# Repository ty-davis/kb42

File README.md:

# kb42
Split 42 key keyboard utilizing Redragon low profile keys

It is heavily inspired by the [Budgy](https://github.com/doesntfazer/Budgy)
while also being influenced in design by the
[Cheapino](https://github.com/tompi/cheapino).

Build guides coming soon. Source code for the firmware
for the keyboard can be found in my [qmk fork](https://github.com/TyGuy60401/qmk_firmware).
In the assets folder you can find some pics and the
.uf2 firmware files that you can download to flash the
board yourself without having to build the entire qmk
compilation suite. One of the firmware files is a via
compatible version of the firmware for the keyboard,
and the other uses a very basic layout which is quite
limited.

Via firmware guide
------------------

Because my firmware isn't in the official via firmware
repo, in order to use via with this keyboard you will
need to follow a few extra steps the first time you
use it.

After flashing the [via specific firmware](https://github.com/TyGuy60401/kb42/blob/3ecddecb2256828aa2ff203ea3fbf5516b5cc939/assets/firmware/kb42_via.uf2)
to the keyboard and connecting the keyboard to your computer,
navigate to the [via website](usevia.app) and press `authorize
device`.  Select kb42 in the dropdown that appears and
you'll enter the app.

Usually you can start changing the keymaps to the board
at this point but we need to complete an extra step. Go to the settings
icon in the top center and enable the option
that says `Show Design Tab`. Now a new paintbrush icon
has appeared above. Select that tab and click `Load
Draft Definition`. That will prompt you to upload a
json file that corresponds to some via specific definitions
for this keyboard. Upload [this json file](https://github.com/TyGuy60401/kb42/blob/dc6ad67e50948e26156101fd82f4def80222cbb4/assets/firmware/kb42_via-definition.json)
which can be found in this repo -> assets -> firmware
-> kb42_via-definition.json

Once that file is uploaded and the via app accepts it
you'll be able to change all of the configuration for
the board. You can see the configuration that I'm using
for the board by uploading the configuration file called
[`kb42_TyGuy60401_layout.json`](https://github.com/TyGuy60401/kb42/blob/dc6ad67e50948e26156101fd82f4def80222cbb4/assets/firmware/kb42_TyGuy60401_layout.json) which can be found in
the firmware folder.

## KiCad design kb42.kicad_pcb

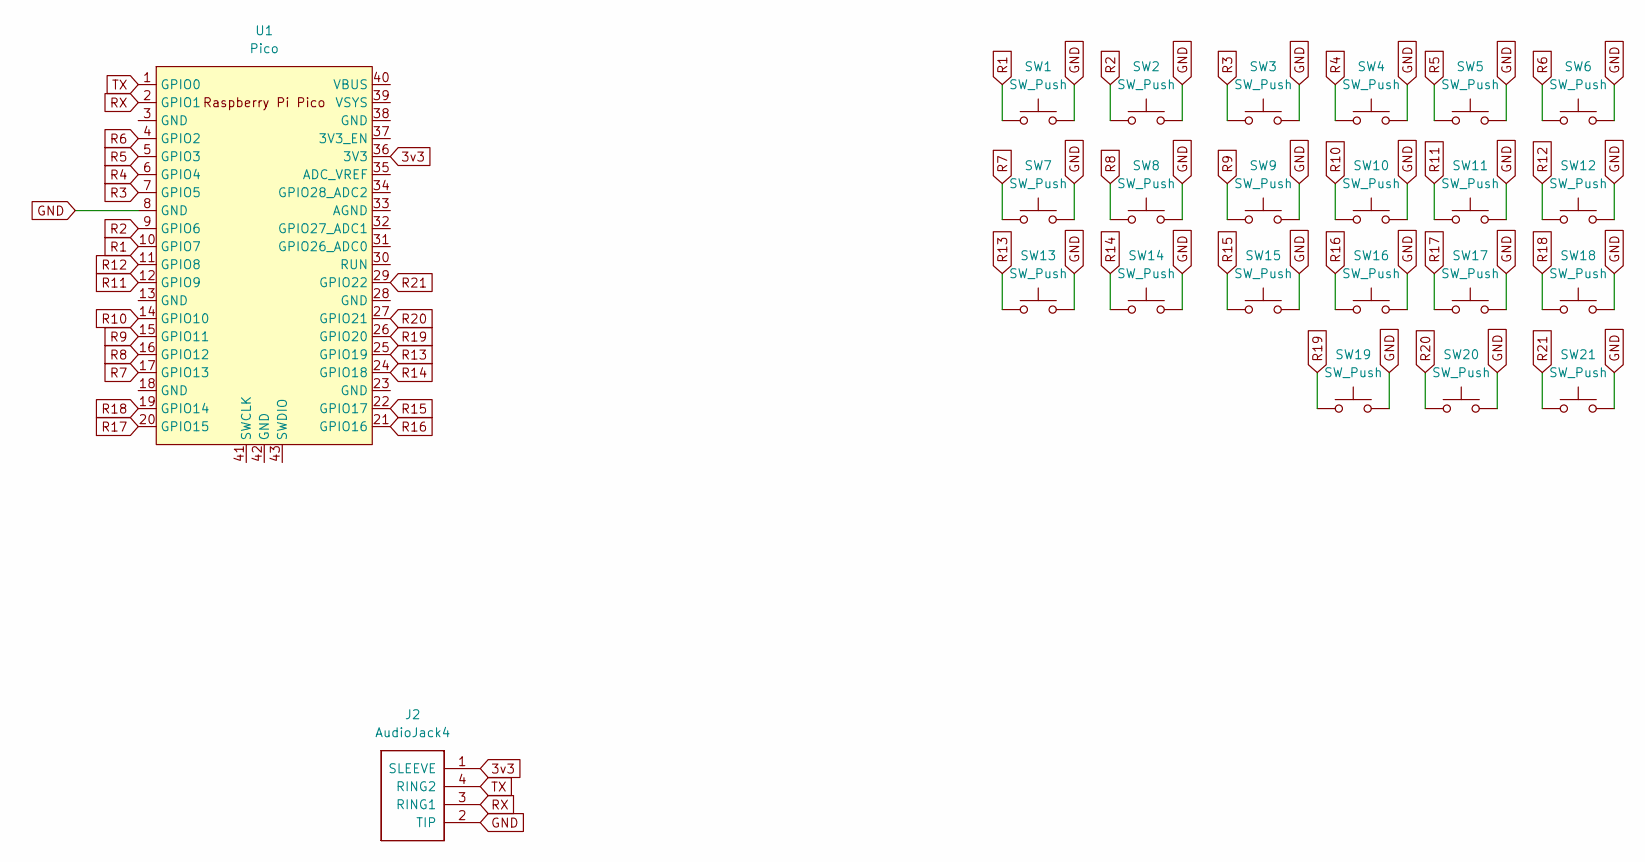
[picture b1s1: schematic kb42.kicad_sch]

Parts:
J2: AudioJack4; TRRS-PJ-320A-rev
SW1, SW2, SW3, SW4, SW5, SW6, SW7, SW8, SW9, SW10, SW11, SW12, SW13, SW14, SW15, SW16, SW17, SW18, SW19, SW20, SW21: SW_Push; SW_Redragon_LowProfile_Reversible_PCB_1.00u
U1: Pico; RPi_Pico_SMD_TH-REV2

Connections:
3v3: J2.1 (SLEEVE), U1.36 (3V3)
GND: J2.2 (TIP), SW1.2, SW2.2, SW3.2, SW4.2, SW5.2, SW6.2, SW7.2, SW8.2, SW9.2, SW10.2, SW11.2, SW12.2, SW13.2, SW14.2, SW15.2, SW16.2, SW17.2, SW18.2, SW19.2, SW20.2, SW21.2, U1.8 (GND)
R1: SW1.1, U1.10 (GPIO7)
R2: SW2.1, U1.9 (GPIO6)
R3: SW3.1, U1.7 (GPIO5)
R4: SW4.1, U1.6 (GPIO4)
R5: SW5.1, U1.5 (GPIO3)
R6: SW6.1, U1.4 (GPIO2)
R7: SW7.1, U1.17 (GPIO13)
R8: SW8.1, U1.16 (GPIO12)
R9: SW9.1, U1.15 (GPIO11)
R10: SW10.1, U1.14 (GPIO10)
R11: SW11.1, U1.12 (GPIO9)
R12: SW12.1, U1.11 (GPIO8)
R13: SW13.1, U1.25 (GPIO19)
R14: SW14.1, U1.24 (GPIO18)
R15: SW15.1, U1.22 (GPIO17)
R16: SW16.1, U1.21 (GPIO16)
R17: SW17.1, U1.20 (GPIO15)
R18: SW18.1, U1.19 (GPIO14)
R19: SW19.1, U1.26 (GPIO20)
R20: SW20.1, U1.27 (GPIO21)
R21: SW21.1, U1.29 (GPIO22)
RX: J2.3 (RING1), U1.2 (GPIO1)
TX: J2.4 (RING2), U1.1 (GPIO0)

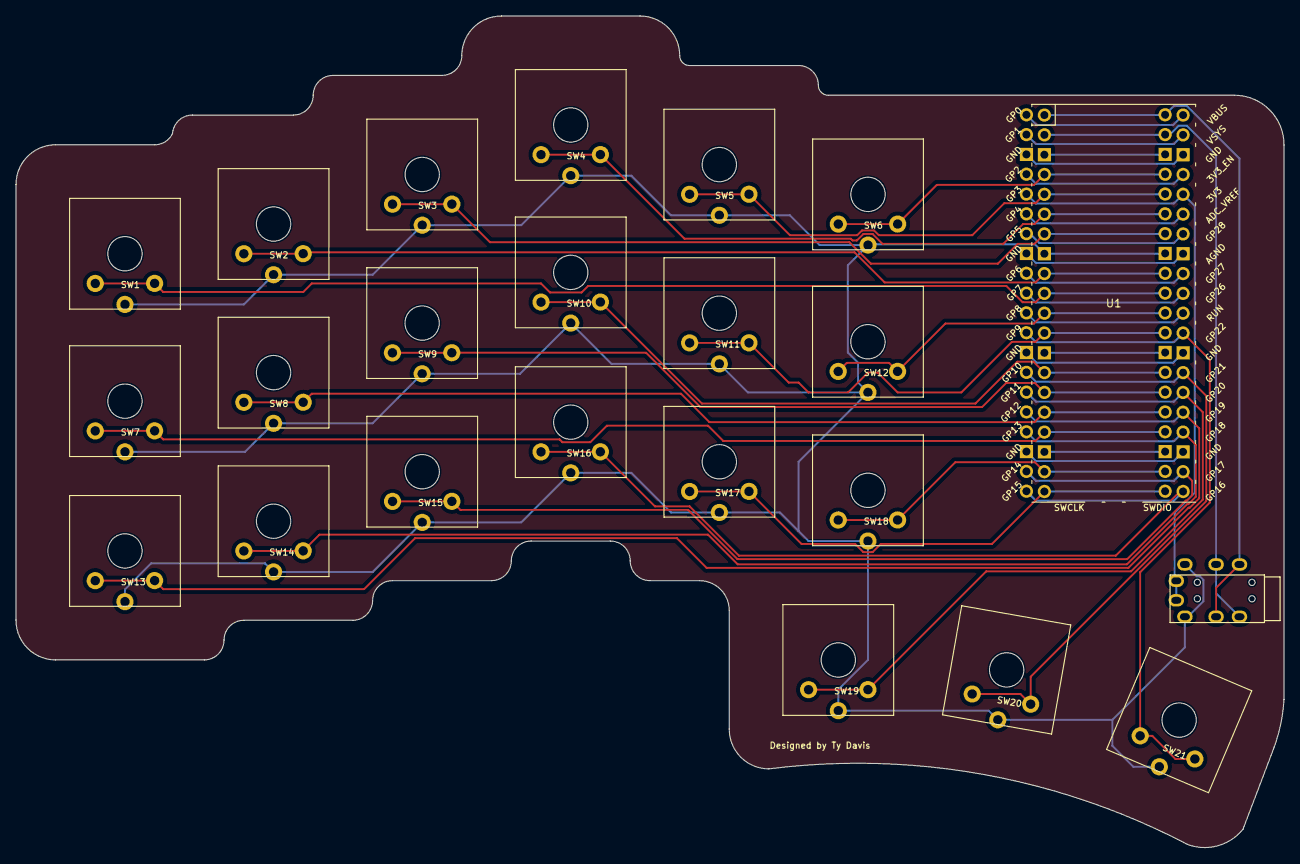
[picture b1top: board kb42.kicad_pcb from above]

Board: 2 copper layers, 162.6 x 106.6 mm, 23 parts (0 on the bottom side), 25 nets.

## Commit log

2024-02-16 Initial commit and Rev1 of the kb42
2024-02-16 Another commit
2024-02-16 Uploading an image
2024-03-12 Updating the readme and pushing the firmware to the firmware folder
2024-03-16 Added a new files for via configuration
2024-03-16 Made the via portion of the readme just a little bit better
2025-01-14 Likely the final update here. Going to start on a v2 now.
